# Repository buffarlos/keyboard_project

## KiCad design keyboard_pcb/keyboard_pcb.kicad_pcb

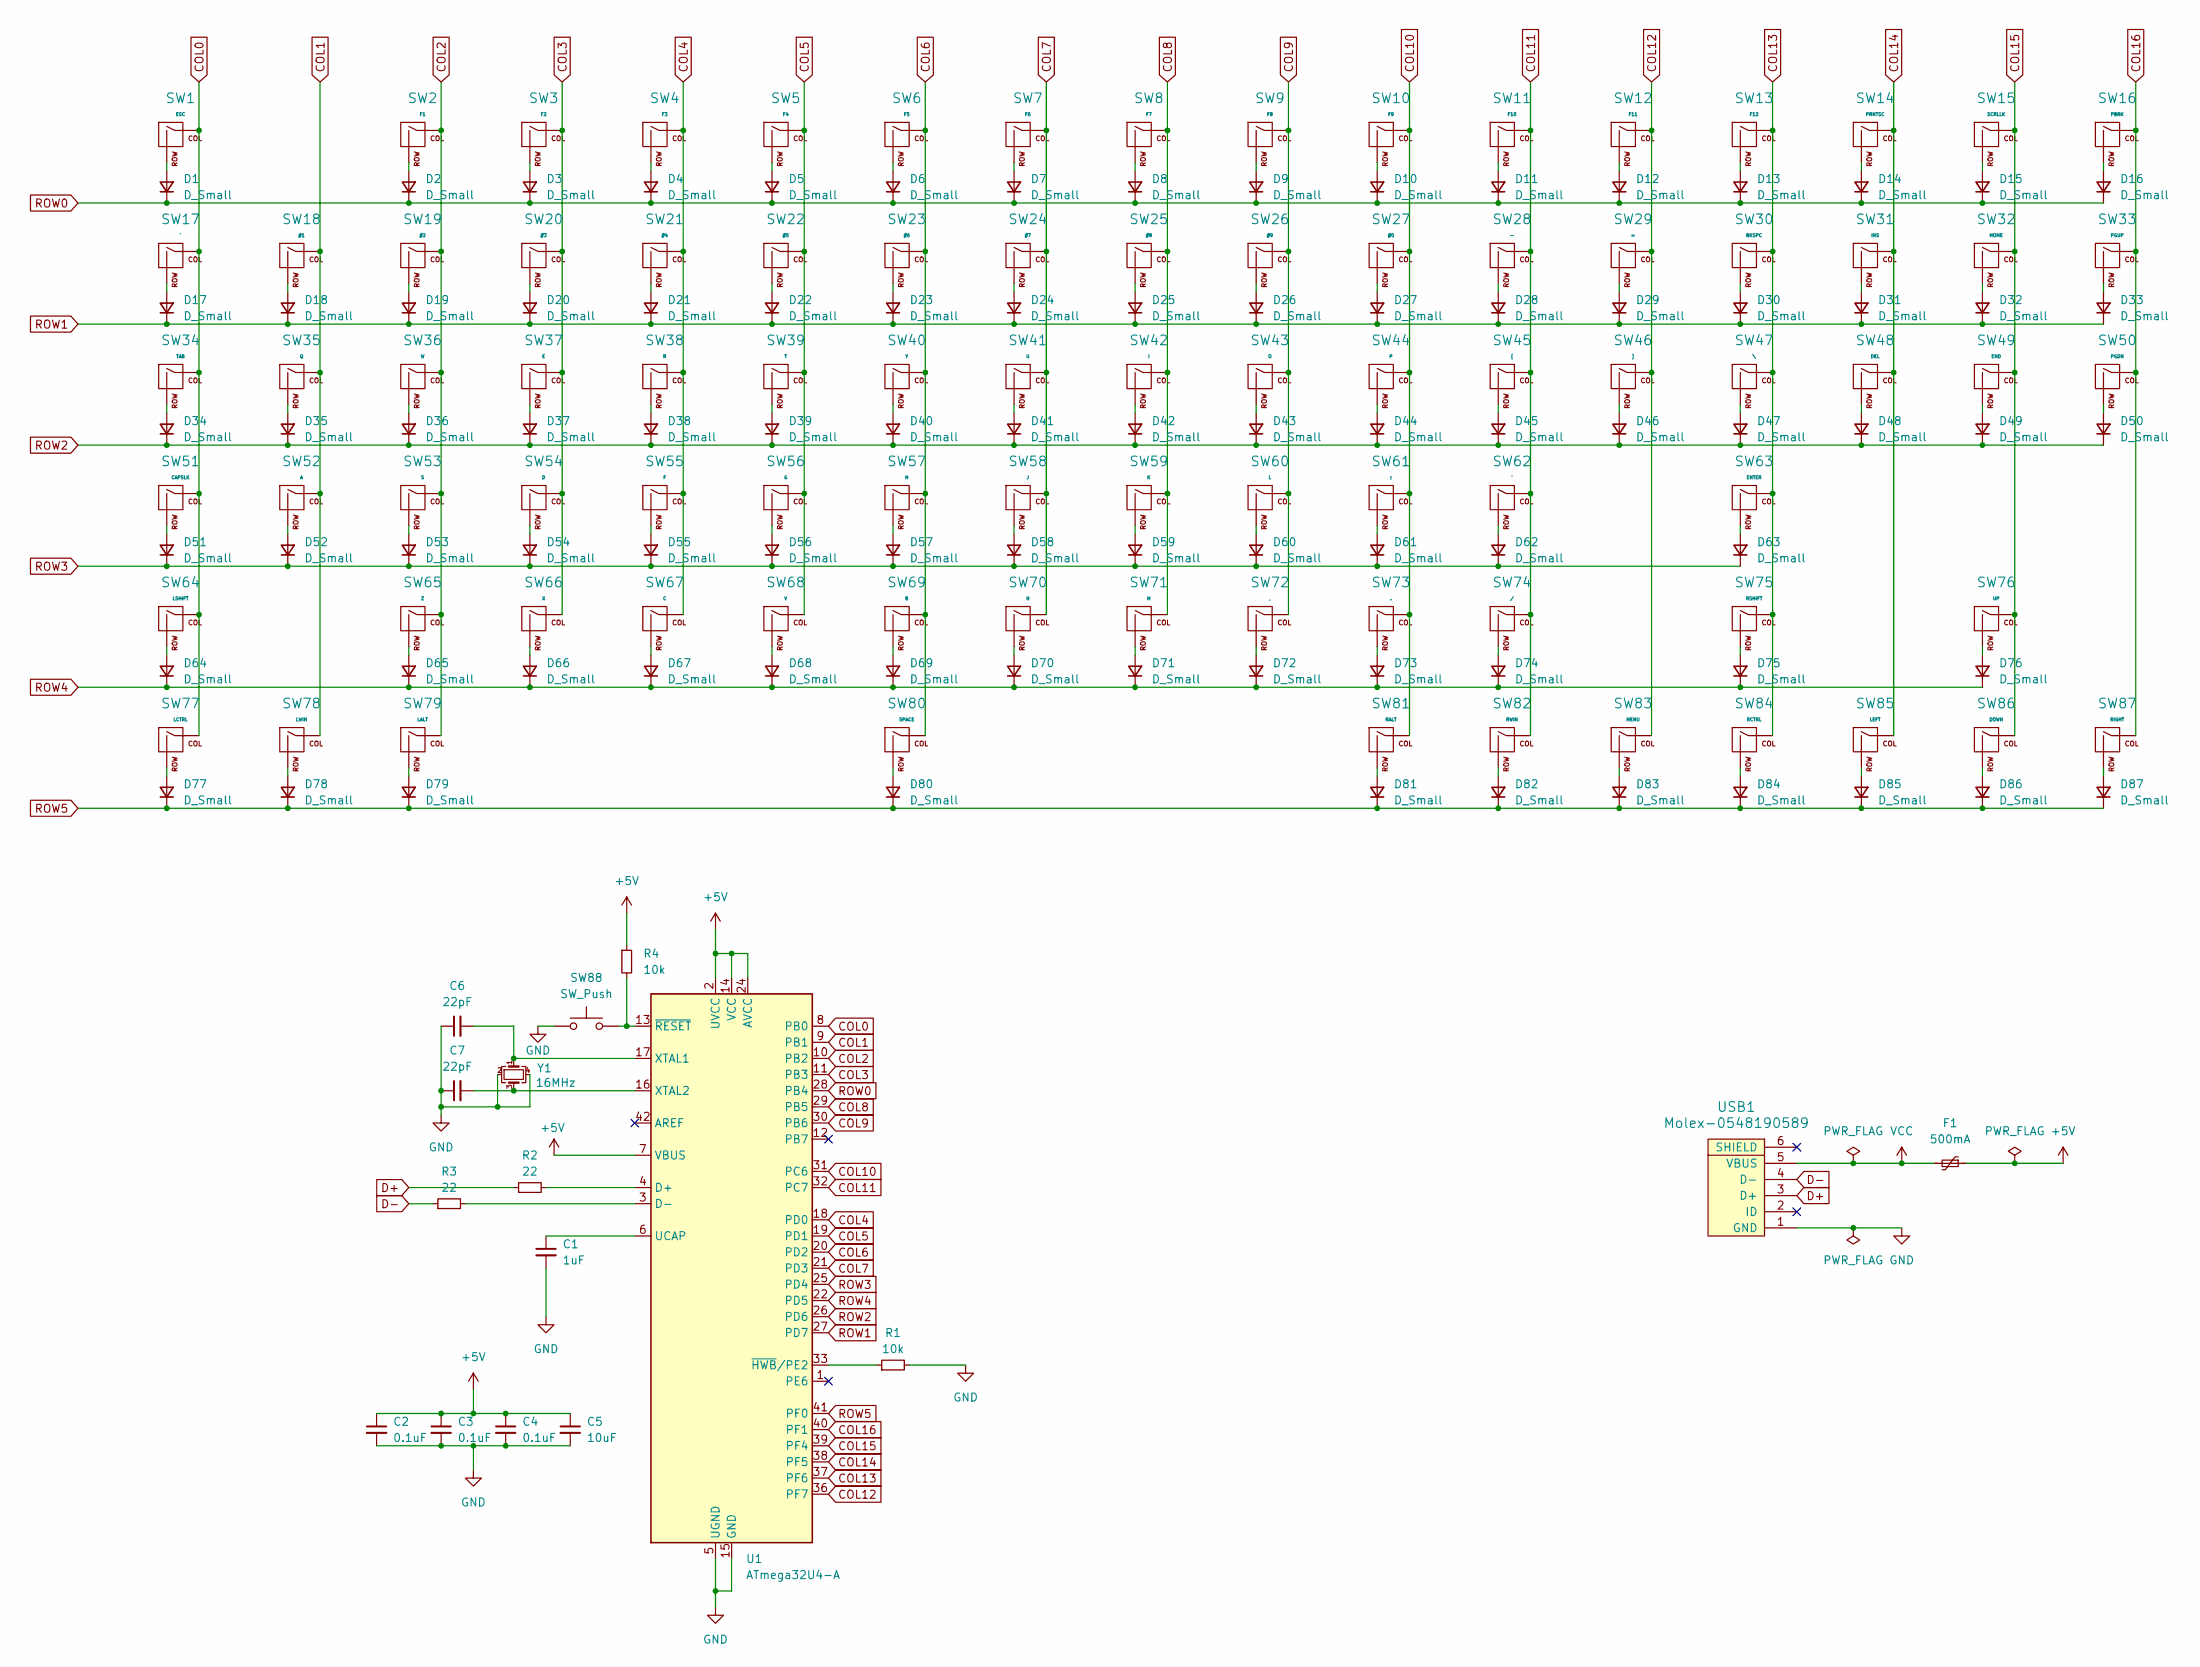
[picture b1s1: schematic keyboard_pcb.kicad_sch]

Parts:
C1: 1uF; C_0805_2012Metric_Pad1.18x1.45mm_HandSolder
C2, C3, C4: 0.1uF; C_0805_2012Metric_Pad1.18x1.45mm_HandSolder
C5: 10uF; C_0805_2012Metric_Pad1.18x1.45mm_HandSolder
C6, C7: 22pF; C_0805_2012Metric_Pad1.18x1.45mm_HandSolder
D1, D2, D3, D4, D5, D6, D7, D8, D9, D10, D11, D12, D13, D14, D15, D16, D17, D18, D19, D20, D21, D22, D23, D24, D25, D26, D27, D28, D29, D30, D31, D32, D33, D34, D35, D36, D37, D38, D39, D40, D41, D42, D43, D44, D45, D46, D47, D48, D49, D50, D51, D52, D53, D54, D55, D56, D57, D58, D59, D60, D61, D62, D63, D64, D65, D66, D67, D68, D69, D70, D71, D72, D73, D74, D75, D76, D77, D78, D79, D80, D81, D82, D83, D84, D85, D86, D87: D_Small; D_SOD-123
F1: 500mA; Fuse_1206_3216Metric_Pad1.42x1.75mm_HandSolder
R1, R4: 10k; R_0805_2012Metric_Pad1.20x1.40mm_HandSolder
R2, R3: 22; R_0805_2012Metric_Pad1.20x1.40mm_HandSolder
SW1: ESC; SW_Cherry_MX_1.00u_PCB
SW2: F1; SW_Cherry_MX_1.00u_PCB
SW3: F2; SW_Cherry_MX_1.00u_PCB
SW4: F3; SW_Cherry_MX_1.00u_PCB
SW5: F4; SW_Cherry_MX_1.00u_PCB
SW6: F5; SW_Cherry_MX_1.00u_PCB
SW7: F6; SW_Cherry_MX_1.00u_PCB
SW8: F7; SW_Cherry_MX_1.00u_PCB
SW9: F8; SW_Cherry_MX_1.00u_PCB
SW10: F9; SW_Cherry_MX_1.00u_PCB
SW11: F10; SW_Cherry_MX_1.00u_PCB
SW12: F11; SW_Cherry_MX_1.00u_PCB
SW13: F12; SW_Cherry_MX_1.00u_PCB
SW14: PRNTSC; SW_Cherry_MX_1.00u_PCB
SW15: SCRLLK; SW_Cherry_MX_1.00u_PCB
SW16: PBRK; SW_Cherry_MX_1.00u_PCB
SW17: `; SW_Cherry_MX_1.00u_PCB
SW18: #1; SW_Cherry_MX_1.00u_PCB
SW19: #2; SW_Cherry_MX_1.00u_PCB
SW20: #3; SW_Cherry_MX_1.00u_PCB
SW21: #4; SW_Cherry_MX_1.00u_PCB
SW22: #5; SW_Cherry_MX_1.00u_PCB
SW23: #6; SW_Cherry_MX_1.00u_PCB
SW24: #7; SW_Cherry_MX_1.00u_PCB
SW25: #8; SW_Cherry_MX_1.00u_PCB
SW26: #9; SW_Cherry_MX_1.00u_PCB
SW27: #0; SW_Cherry_MX_1.00u_PCB
SW28: -; SW_Cherry_MX_1.00u_PCB
SW29: =; SW_Cherry_MX_1.00u_PCB
SW30: BKSPC; SW_Cherry_MX_2.00u_PCB
SW31: INS; SW_Cherry_MX_1.00u_PCB
SW32: HOME; SW_Cherry_MX_1.00u_PCB
SW33: PGUP; SW_Cherry_MX_1.00u_PCB
SW34: TAB; SW_Cherry_MX_1.50u_PCB
SW35: Q; SW_Cherry_MX_1.00u_PCB
SW36: W; SW_Cherry_MX_1.00u_PCB
SW37: E; SW_Cherry_MX_1.00u_PCB
SW38: R; SW_Cherry_MX_1.00u_PCB
SW39: T; SW_Cherry_MX_1.00u_PCB
SW40: Y; SW_Cherry_MX_1.00u_PCB
SW41: U; SW_Cherry_MX_1.00u_PCB
SW42: I; SW_Cherry_MX_1.00u_PCB
SW43: O; SW_Cherry_MX_1.00u_PCB
SW44: P; SW_Cherry_MX_1.00u_PCB
SW45: [; SW_Cherry_MX_1.00u_PCB
SW46: ]; SW_Cherry_MX_1.00u_PCB
SW47: \; SW_Cherry_MX_1.50u_PCB
SW48: DEL; SW_Cherry_MX_1.00u_PCB
SW49: END; SW_Cherry_MX_1.00u_PCB
SW50: PGDN; SW_Cherry_MX_1.00u_PCB
SW51: CAPSLK; SW_Cherry_MX_1.75u_PCB
SW52: A; SW_Cherry_MX_1.00u_PCB
SW53: S; SW_Cherry_MX_1.00u_PCB
SW54: D; SW_Cherry_MX_1.00u_PCB
SW55: F; SW_Cherry_MX_1.00u_PCB
SW56: G; SW_Cherry_MX_1.00u_PCB
SW57: H; SW_Cherry_MX_1.00u_PCB
SW58: J; SW_Cherry_MX_1.00u_PCB
SW59: K; SW_Cherry_MX_1.00u_PCB
SW60: L; SW_Cherry_MX_1.00u_PCB
SW61: ;; SW_Cherry_MX_1.00u_PCB
SW62: '; SW_Cherry_MX_1.00u_PCB
SW63: ENTER; SW_Cherry_MX_2.25u_PCB
SW64: LSHIFT; SW_Cherry_MX_2.25u_PCB
SW65: Z; SW_Cherry_MX_1.00u_PCB
SW66: X; SW_Cherry_MX_1.00u_PCB
SW67: C; SW_Cherry_MX_1.00u_PCB
SW68: V; SW_Cherry_MX_1.00u_PCB
SW69: B; SW_Cherry_MX_1.00u_PCB
SW70: N; SW_Cherry_MX_1.00u_PCB
SW71: M; SW_Cherry_MX_1.00u_PCB
SW72: ,; SW_Cherry_MX_1.00u_PCB
SW73: .; SW_Cherry_MX_1.00u_PCB
SW74: /; SW_Cherry_MX_1.00u_PCB
SW75: RSHIFT; SW_Cherry_MX_2.75u_PCB
SW76: UP; SW_Cherry_MX_1.00u_PCB
SW77: LCTRL; SW_Cherry_MX_1.25u_PCB
SW78: LWIN; SW_Cherry_MX_1.25u_PCB
SW79: LALT; SW_Cherry_MX_1.25u_PCB
SW80: SPACE; SW_Cherry_MX_6.25u_PCB
SW81: RALT; SW_Cherry_MX_1.25u_PCB
SW82: RWIN; SW_Cherry_MX_1.25u_PCB
SW83: MENU; SW_Cherry_MX_1.25u_PCB
SW84: RCTRL; SW_Cherry_MX_1.25u_PCB
SW85: LEFT; SW_Cherry_MX_1.00u_PCB
SW86: DOWN; SW_Cherry_MX_1.00u_PCB
SW87: RIGHT; SW_Cherry_MX_1.00u_PCB
SW88: SW_Push; SW_SPST_SKQG_WithStem
U1: ATmega32U4-A; TQFP-44_10x10mm_P0.8mm
USB1: Molex-0548190589
Y1: 16MHz; Crystal_SMD_3225-4Pin_3.2x2.5mm_HandSoldering

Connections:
+5V: C2.1, C3.1, C4.1, C5.1, F1.1, R4.1, U1.2 (UVCC), U1.7 (VBUS), U1.14 (VCC), U1.24 (AVCC), U1.34 (VCC), U1.44 (AVCC)
COL0: SW1.1 (COL), SW17.1 (COL), SW34.1 (COL), SW51.1 (COL), SW64.1 (COL), SW77.1 (COL), U1.8 (PB0)
COL1: SW18.1 (COL), SW35.1 (COL), SW52.1 (COL), SW78.1 (COL), U1.9 (PB1)
COL2: SW2.1 (COL), SW19.1 (COL), SW36.1 (COL), SW53.1 (COL), SW65.1 (COL), SW79.1 (COL), U1.10 (PB2)
COL3: SW3.1 (COL), SW20.1 (COL), SW37.1 (COL), SW54.1 (COL), SW66.1 (COL), U1.11 (PB3)
COL4: SW4.1 (COL), SW21.1 (COL), SW38.1 (COL), SW55.1 (COL), SW67.1 (COL), U1.18 (PD0)
COL5: SW5.1 (COL), SW22.1 (COL), SW39.1 (COL), SW56.1 (COL), SW68.1 (COL), U1.19 (PD1)
COL6: SW6.1 (COL), SW23.1 (COL), SW40.1 (COL), SW57.1 (COL), SW69.1 (COL), SW80.1 (COL), U1.20 (PD2)
COL7: SW7.1 (COL), SW24.1 (COL), SW41.1 (COL), SW58.1 (COL), SW70.1 (COL), U1.21 (PD3)
COL8: SW8.1 (COL), SW25.1 (COL), SW42.1 (COL), SW59.1 (COL), SW71.1 (COL), U1.29 (PB5)
COL9: SW9.1 (COL), SW26.1 (COL), SW43.1 (COL), SW60.1 (COL), SW72.1 (COL), U1.30 (PB6)
COL10: SW10.1 (COL), SW27.1 (COL), SW44.1 (COL), SW61.1 (COL), SW73.1 (COL), SW81.1 (COL), U1.31 (PC6)
COL11: SW11.1 (COL), SW28.1 (COL), SW45.1 (COL), SW62.1 (COL), SW74.1 (COL), SW82.1 (COL), U1.32 (PC7)
COL12: SW12.1 (COL), SW29.1 (COL), SW46.1 (COL), SW83.1 (COL), U1.36 (PF7)
COL13: SW13.1 (COL), SW30.1 (COL), SW47.1 (COL), SW63.1 (COL), SW75.1 (COL), SW84.1 (COL), U1.37 (PF6)
COL14: SW14.1 (COL), SW31.1 (COL), SW48.1 (COL), SW85.1 (COL), U1.38 (PF5)
COL15: SW15.1 (COL), SW32.1 (COL), SW49.1 (COL), SW76.1 (COL), SW86.1 (COL), U1.39 (PF4)
COL16: SW16.1 (COL), SW33.1 (COL), SW50.1 (COL), SW87.1 (COL), U1.40 (PF1)
D+: R2.1, USB1.3 (D+)
D-: R3.1, USB1.4 (D-)
GND: C1.2, C2.2, C3.2, C4.2, C5.2, C6.1, C7.1, R1.2, SW88.1, U1.5 (UGND), U1.15 (GND), U1.23 (GND), U1.35 (GND), U1.43 (GND), USB1.1 (GND), Y1.2, Y1.4
unnamed: D1.2 (A), SW1.2 (ROW)
unnamed: D2.2 (A), SW2.2 (ROW)
unnamed: D3.2 (A), SW3.2 (ROW)
unnamed: D4.2 (A), SW4.2 (ROW)
unnamed: D5.2 (A), SW5.2 (ROW)
unnamed: D6.2 (A), SW6.2 (ROW)
unnamed: D7.2 (A), SW7.2 (ROW)
unnamed: D8.2 (A), SW8.2 (ROW)
unnamed: D9.2 (A), SW9.2 (ROW)
unnamed: D10.2 (A), SW10.2 (ROW)
unnamed: D11.2 (A), SW11.2 (ROW)
unnamed: D12.2 (A), SW12.2 (ROW)
unnamed: D13.2 (A), SW13.2 (ROW)
unnamed: D14.2 (A), SW14.2 (ROW)
unnamed: D15.2 (A), SW15.2 (ROW)
unnamed: D16.2 (A), SW16.2 (ROW)
unnamed: D17.2 (A), SW17.2 (ROW)
unnamed: D18.2 (A), SW18.2 (ROW)
unnamed: D19.2 (A), SW19.2 (ROW)
unnamed: D20.2 (A), SW20.2 (ROW)
unnamed: D21.2 (A), SW21.2 (ROW)
unnamed: D22.2 (A), SW22.2 (ROW)
unnamed: D23.2 (A), SW23.2 (ROW)
unnamed: D24.2 (A), SW24.2 (ROW)
unnamed: D25.2 (A), SW25.2 (ROW)
unnamed: D26.2 (A), SW26.2 (ROW)
unnamed: D27.2 (A), SW27.2 (ROW)
unnamed: D28.2 (A), SW28.2 (ROW)
unnamed: D29.2 (A), SW29.2 (ROW)
unnamed: D30.2 (A), SW30.2 (ROW)
unnamed: D31.2 (A), SW31.2 (ROW)
unnamed: D32.2 (A), SW32.2 (ROW)
unnamed: D33.2 (A), SW33.2 (ROW)
unnamed: D34.2 (A), SW34.2 (ROW)
unnamed: D35.2 (A), SW35.2 (ROW)
unnamed: D36.2 (A), SW36.2 (ROW)
unnamed: D37.2 (A), SW37.2 (ROW)
unnamed: D38.2 (A), SW38.2 (ROW)
unnamed: D39.2 (A), SW39.2 (ROW)
unnamed: D40.2 (A), SW40.2 (ROW)
unnamed: D41.2 (A), SW41.2 (ROW)
unnamed: D42.2 (A), SW42.2 (ROW)
unnamed: D43.2 (A), SW43.2 (ROW)
unnamed: D44.2 (A), SW44.2 (ROW)
unnamed: D45.2 (A), SW45.2 (ROW)
unnamed: D46.2 (A), SW46.2 (ROW)
unnamed: D47.2 (A), SW47.2 (ROW)
unnamed: D48.2 (A), SW48.2 (ROW)
unnamed: D49.2 (A), SW49.2 (ROW)
unnamed: D50.2 (A), SW50.2 (ROW)
unnamed: D51.2 (A), SW51.2 (ROW)
unnamed: D52.2 (A), SW52.2 (ROW)
unnamed: D53.2 (A), SW53.2 (ROW)
unnamed: D54.2 (A), SW54.2 (ROW)
unnamed: D55.2 (A), SW55.2 (ROW)
unnamed: D56.2 (A), SW56.2 (ROW)
unnamed: D57.2 (A), SW57.2 (ROW)
unnamed: D58.2 (A), SW58.2 (ROW)
unnamed: D59.2 (A), SW59.2 (ROW)
unnamed: D60.2 (A), SW60.2 (ROW)
unnamed: D61.2 (A), SW61.2 (ROW)
unnamed: D62.2 (A), SW62.2 (ROW)
unnamed: D63.2 (A), SW63.2 (ROW)
unnamed: D64.2 (A), SW64.2 (ROW)
unnamed: D65.2 (A), SW65.2 (ROW)
unnamed: D66.2 (A), SW66.2 (ROW)
unnamed: D67.2 (A), SW67.2 (ROW)
unnamed: D68.2 (A), SW68.2 (ROW)
unnamed: D69.2 (A), SW69.2 (ROW)
unnamed: D70.2 (A), SW70.2 (ROW)
unnamed: D71.2 (A), SW71.2 (ROW)
unnamed: D72.2 (A), SW72.2 (ROW)
unnamed: D73.2 (A), SW73.2 (ROW)
unnamed: D74.2 (A), SW74.2 (ROW)
unnamed: D75.2 (A), SW75.2 (ROW)
unnamed: D76.2 (A), SW76.2 (ROW)
unnamed: D77.2 (A), SW77.2 (ROW)
unnamed: D78.2 (A), SW78.2 (ROW)
unnamed: D79.2 (A), SW79.2 (ROW)
unnamed: D80.2 (A), SW80.2 (ROW)
unnamed: D81.2 (A), SW81.2 (ROW)
unnamed: D82.2 (A), SW82.2 (ROW)
unnamed: D83.2 (A), SW83.2 (ROW)
unnamed: D84.2 (A), SW84.2 (ROW)
unnamed: D85.2 (A), SW85.2 (ROW)
unnamed: D86.2 (A), SW86.2 (ROW)
unnamed: D87.2 (A), SW87.2 (ROW)
unnamed: R2.2, U1.4 (D+)
unnamed: R3.2, U1.3 (D-)
unnamed: C1.1, U1.6 (UCAP)
unnamed: C6.2, U1.17 (XTAL1), Y1.1
unnamed: C7.2, U1.16 (XTAL2), Y1.3
unnamed: R1.1, U1.33 (~HWB/PE2)
unnamed: R4.2, SW88.2, U1.13 (~RESET)
ROW0: D1.1 (K), D2.1 (K), D3.1 (K), D4.1 (K), D5.1 (K), D6.1 (K), D7.1 (K), D8.1 (K), D9.1 (K), D10.1 (K), D11.1 (K), D12.1 (K), D13.1 (K), D14.1 (K), D15.1 (K), D16.1 (K), U1.28 (PB4)
ROW1: D17.1 (K), D18.1 (K), D19.1 (K), D20.1 (K), D21.1 (K), D22.1 (K), D23.1 (K), D24.1 (K), D25.1 (K), D26.1 (K), D27.1 (K), D28.1 (K), D29.1 (K), D30.1 (K), D31.1 (K), D32.1 (K), D33.1 (K), U1.27 (PD7)
ROW2: D34.1 (K), D35.1 (K), D36.1 (K), D37.1 (K), D38.1 (K), D39.1 (K), D40.1 (K), D41.1 (K), D42.1 (K), D43.1 (K), D44.1 (K), D45.1 (K), D46.1 (K), D47.1 (K), D48.1 (K), D49.1 (K), D50.1 (K), U1.26 (PD6)
ROW3: D51.1 (K), D52.1 (K), D53.1 (K), D54.1 (K), D55.1 (K), D56.1 (K), D57.1 (K), D58.1 (K), D59.1 (K), D60.1 (K), D61.1 (K), D62.1 (K), D63.1 (K), U1.25 (PD4)
ROW4: D64.1 (K), D65.1 (K), D66.1 (K), D67.1 (K), D68.1 (K), D69.1 (K), D70.1 (K), D71.1 (K), D72.1 (K), D73.1 (K), D74.1 (K), D75.1 (K), D76.1 (K), U1.22 (PD5)
ROW5: D77.1 (K), D78.1 (K), D79.1 (K), D80.1 (K), D81.1 (K), D82.1 (K), D83.1 (K), D84.1 (K), D85.1 (K), D86.1 (K), D87.1 (K), U1.41 (PF0)
VCC: F1.2, USB1.5 (VBUS)

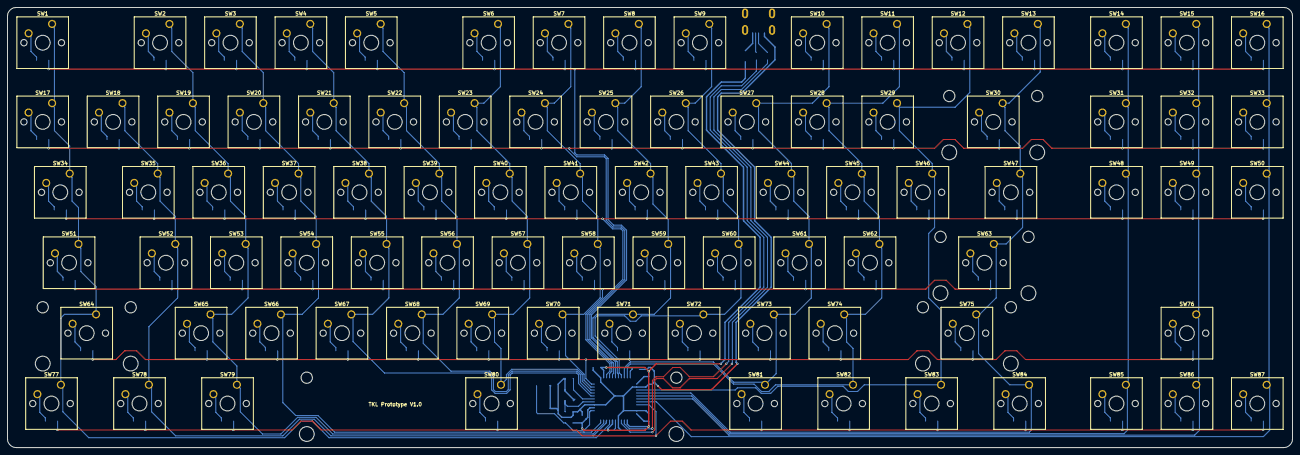
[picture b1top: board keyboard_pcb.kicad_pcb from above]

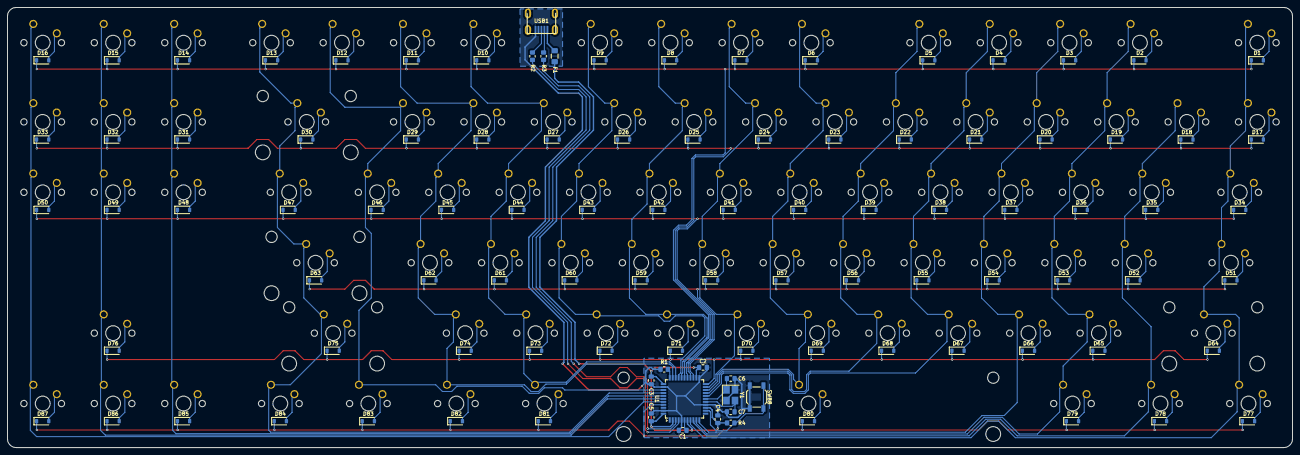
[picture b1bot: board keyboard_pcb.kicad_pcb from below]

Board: 2 copper layers, 347.7 x 119.1 mm, 190 parts (103 on the bottom side), 122 nets.

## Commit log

2024-09-20 Initial commit with KiCad project file
2024-09-20 Added keyboard specific KiCad library submodules
2024-09-20 Added keyboard specific KiCad footprints and schematics
2024-09-20 Schematic first draft
2024-09-21 Complete electronic schematic
2024-09-21 PCB layout first draft
2024-09-22 Finalize key switch positions
2024-09-22 Add row/column traces
2024-09-22 MCU routing except row/column
2024-09-22 PCB complete routing
2024-09-22 PCB cleanup
2024-09-22 Gerber file generated
2024-09-22 TKL Prototype V1.0
